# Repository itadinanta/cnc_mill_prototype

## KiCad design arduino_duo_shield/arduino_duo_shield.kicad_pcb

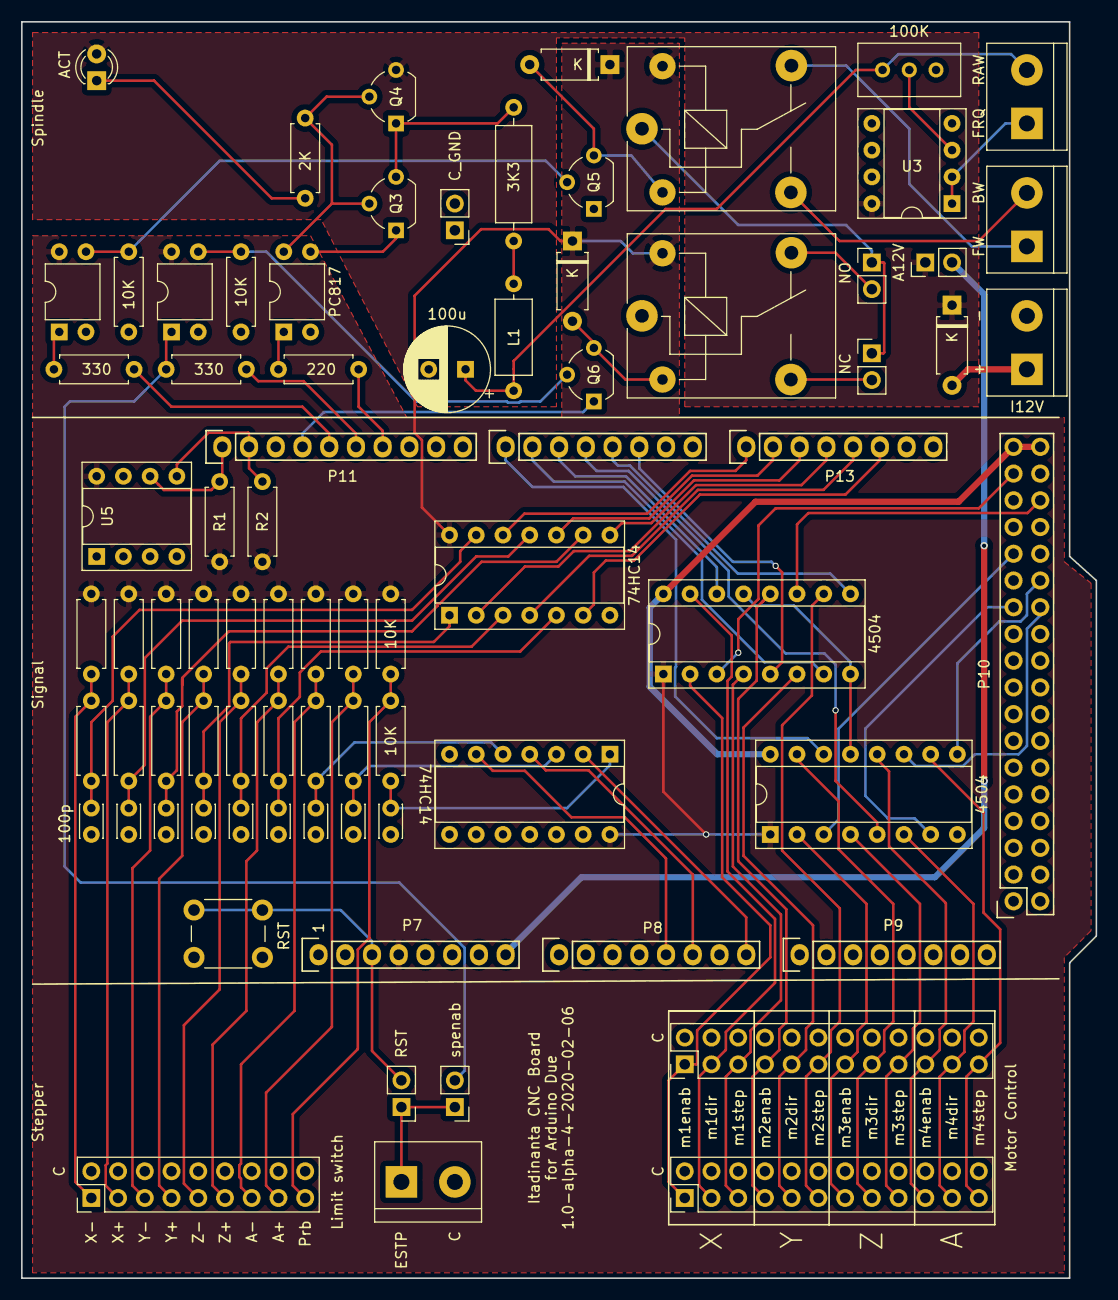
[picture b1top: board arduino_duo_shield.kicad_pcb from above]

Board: 2 copper layers, 102.1 x 119.4 mm, 79 parts (0 on the bottom side), 84 nets.

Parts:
C2, C3, C4, C5, C6, C7, C9, C10, C11: 100p; C_Disc_D3.0mm_W2.0mm_P2.50mm
C8: 100u; CP_Radial_D8.0mm_P3.50mm
D1: LED; LED_D3.0mm
D3, D4, D5: 1N4007; D_A-405_P7.62mm_Horizontal
J2: EStop; TerminalBlock_bornier-2_P5.08mm
J3: Motor_Control; PinHeader_2x12_P2.54mm_Vertical
J4: Limit_Switches; PinHeader_2x09_P2.54mm_Vertical
J5: inverter_freq; TerminalBlock_bornier-2_P5.08mm
J6: inverter_cmd; TerminalBlock_bornier-2_P5.08mm
J8: inverter_power; TerminalBlock_bornier-2_P5.08mm
J9: Motor_Control_Mirror; PinHeader_2x12_P2.54mm_Vertical
JP1, JP2, JP3, JP4: Jumper_NC_Small; PinHeader_1x02_P2.54mm_Vertical
JP5: EStop_RST; PinHeader_1x02_P2.54mm_Vertical
JP6: EStop_spenab; PinHeader_1x02_P2.54mm_Vertical
K2, K3: JQC-3F; Relay_SPDT_SANYOU_SRD_Series_Form_C
L1: 1m; L_Axial_L7.0mm_D3.3mm_P10.16mm_Horizontal_Fastron_MICC
P7: Power; Socket_Strip_Arduino_1x08
P8, P9: Analog; Socket_Strip_Arduino_1x08
P10: Digital; Socket_Strip_Arduino_2x18
P11: PWM; Socket_Strip_Arduino_1x10
P12: PWM; Socket_Strip_Arduino_1x08
P13: Communication; Socket_Strip_Arduino_1x08
Q3, Q5, Q6: 2N7000; TO-92_Wide
Q4: BS250; TO-92_Wide
R1, R2: 1K5; R_Axial_DIN0207_L6.3mm_D2.5mm_P7.62mm_Horizontal
R3, R4, R5, R6, R7, R8, R9, R10, R11, R12, R13, R14, R19, R20, R25, R26, R27, R28, R29, R30: 10K; R_Axial_DIN0207_L6.3mm_D2.5mm_P7.62mm_Horizontal
R15: 220; R_Axial_DIN0207_L6.3mm_D2.5mm_P7.62mm_Horizontal
R21: 2K; R_Axial_DIN0207_L6.3mm_D2.5mm_P7.62mm_Horizontal
R22, R24: 330; R_Axial_DIN0207_L6.3mm_D2.5mm_P7.62mm_Horizontal
R23: 3K3; R_Axial_DIN0309_L9.0mm_D3.2mm_P12.70mm_Horizontal
RV1: 100K; Potentiometer_Bourns_3296W_Vertical
SW1: SW_Push; SW_PUSH_6mm
U1, U2: 4504; DIP-16_W7.62mm_Socket
U3: LM358; DIP-8_W7.62mm_Socket
U4, U6: 74HC14; DIP-14_W7.62mm_Socket
U5: 24LC16; DIP-8_W7.62mm_Socket
U7, U8, U9: PC817; DIP-4_W7.62mm

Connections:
+3V3: D3.1, D4.1, K2.5, K3.5, P7.4, R1.2, R2.1, R3.2, R5.2, R7.2, R9.2, R11.2, R13.2, R19.2, R27.2, R29.2, U1.1, U2.1, U4.14, U5.8, U6.14, U8.4, U9.4
+5V: P10.35, P10.36, U1.16, U2.16
/Debounce_x6/SWAmax+: J4.15, R27.1, R28.2
/Debounce_x6/SWAmin+: J4.13, R29.1, R30.2
/Debounce_x6/SWProbe+: J4.17, R19.1, R20.2
/Debounce_x6/SWXmax+: J4.3, R11.1, R12.2
/Debounce_x6/SWXmin+: J4.1, R13.1, R14.2
/Debounce_x6/SWYmax+: J4.7, R7.1, R8.2
/Debounce_x6/SWYmin+: J4.5, R9.1, R10.2
/Debounce_x6/SWZmax+: J4.11, R3.1, R4.2
/Debounce_x6/SWZmin+: J4.9, R5.1, R6.2
/Level_Shifter/hi_1_1: J3.1, J9.1, U1.2
/Level_Shifter/hi_1_2: J3.3, J9.3, U1.15
/Level_Shifter/hi_1_3: J3.5, J9.5, U1.4
/Level_Shifter/hi_1_4: J3.7, J9.7, U1.12
/Level_Shifter/hi_1_5: J3.9, J9.9, U1.6
/Level_Shifter/hi_1_6: J3.11, J9.11, U1.10
/Level_Shifter/hi_2_1: J3.13, J9.13, U2.2
/Level_Shifter/hi_2_2: J3.15, J9.15, U2.15
/Level_Shifter/hi_2_3: J3.17, J9.17, U2.4
/Level_Shifter/hi_2_4: J3.19, J9.19, U2.12
/Level_Shifter/hi_2_5: J3.21, J9.21, U2.6
/Level_Shifter/hi_2_6: J3.23, J9.23, U2.10
/Reset: JP5.2, P7.3, SW1.2
/SCL: P11.1, R1.1, U5.6
/SDA: P11.2, R2.2, U5.5
/Spindle_VFD_Control/I_PWRSAFE: D1.2, D5.1, JP4.1, Q4.3, U3.8
/Spindle_VFD_Control/ext_estop: JP6.2, R24.2, U9.1
/Spindle_VFD_Control/inverter_12V: D5.2, J8.1
/Spindle_VFD_Control/inverter_bw_switch: J6.2, K3.3
/Spindle_VFD_Control/inverter_frequency_10V: J5.1, U3.1, U3.2
/Spindle_VFD_Control/inverter_frequency_raw_10V: C8.1, J5.2, L1.2, RV1.1
/Spindle_VFD_Control/inverter_fw_switch: J6.1, K3.4
/Spindle_VFD_Control/inverter_gnd: C8.2, J8.2, JP1.1, K2.1, Q3.1, RV1.3, U3.4, U7.3
Amn: P8.5, U6.6
Amx: P8.6, U6.4
GND: C2.1, C3.1, C4.1, C5.1, C6.1, C7.1, C9.1, C10.1, C11.1, J2.2, J3.2, J3.4, J3.6, J3.8, J3.10, J3.12, J3.14, J3.16, J3.18, J3.20, J3.22, J3.24, J4.2, J4.4, J4.6, J4.8, J4.10, J4.12, J4.14, J4.16, J4.18, J9.2, J9.4, J9.6, J9.8, J9.10, J9.12, J9.14, J9.16, J9.18, J9.20, J9.22, J9.24, JP1.2, P7.6, P7.7, P10.1, P10.2, P11.4, Q5.1, Q6.1, R25.2, R26.2, SW1.1, U1.8, U1.13, U2.8, U2.13, U4.7, U5.4, U5.7, U6.7, U7.2, U8.2, U9.2
unnamed: C2.2, R4.1, U4.5
unnamed: C3.2, R6.1, U4.3
unnamed: C4.2, R8.1, U4.1
unnamed: C5.2, R10.1, U4.9
unnamed: C6.2, R12.1, U4.11
unnamed: C7.2, R14.1, U4.13
unnamed: C9.2, R20.1, U6.1
unnamed: C10.2, R28.1, U6.3
unnamed: C11.2, R30.1, U6.5
unnamed: D1.1, R21.1
unnamed: D3.2, K3.2, Q5.3
unnamed: D4.2, K2.2, Q6.3
unnamed: J2.1, JP5.1, JP6.1
unnamed: JP2.1, JP3.1, K3.1
unnamed: JP2.2, K2.3
unnamed: JP3.2, K2.4
unnamed: L1.1, R23.2
unnamed: Q3.2, Q4.2, R21.2, U7.4
unnamed: Q3.3, Q4.1, R23.1
unnamed: Q5.2, R25.1, U8.3
unnamed: Q6.2, R26.1, U9.3
unnamed: R15.2, U7.1
unnamed: R22.2, U8.1
unnamed: RV1.2, U3.3
Probe: P8.8, U6.2
Xmn: P13.1, U4.12
Xmx: P13.2, U4.10
Ymn: P13.3, U4.8
Ymx: P13.4, U4.2
Zmn: P13.5, U4.4
Zmx: P13.6, U4.6
ext_12v: JP4.2, P7.8
m1dir: P12.3, U1.14
m1enab: P10.33, U1.3
m1step: P12.6, U1.5
m2dir: P12.2, U1.7
m2enab: P10.32, U1.11
m2step: P12.5, U1.9
m3dir: P12.1, U2.14
m3enab: P10.27, U2.3
m3step: P12.4, U2.5
m4dir: P10.23, U2.7
m4enab: P10.24, U2.11
m4step: P10.26, U2.9
spdir: P11.5, R22.1
spenab: P11.6, R24.1
sppwm: P11.7, R15.1

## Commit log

2019-07-20 Added holes as pockets
2019-07-21 Basic C-Beam profile
2019-07-21 Adds corner side by side
2019-07-23 Last V-slot sketch
2019-08-21 Add debounce x6 for limit switches
2019-08-31 Add labels and footprints
2019-09-01 Replace 4x 6x connectors with 1x 24x, add firmware
2019-09-02 Add firmware to fix the power-on bug
2019-09-06 Fixed power pins
2019-09-11 Use only 1 VPOW in spindle control
2019-09-12 Power block to PCB
2019-09-14 Add PCB front/back for spindle controls
2019-09-21 Complete wiring
2019-09-22 Plot layouts to upload to to JLBPCB
2019-10-07 Add ketch for box container
2019-10-12 Fix diode symbol in schematic
2019-11-03 Add physical workbench diagrams
2019-11-03 Shoulder
2019-11-04 Complete workbench frame sketches
2019-11-04 CAD plans
2019-11-09 Test cuts (mostly flattening)
2019-11-20 Prototype filter-based PWM->voltage DAC
2019-11-25 Add sketch for the spindle bracket adapter
2019-12-04 Recalculate paths of spindle adapter
2019-12-23 Ready to build the WorkBee
2019-12-23 Add signal mirror and control jumpers
2019-12-27 Add design and paths for simple inverter holding panel
2019-12-29 Route all paths
2019-12-29 Add silk screen labels and version number
2019-12-30 Generate gerber files for 1.0-alpha-1
2019-12-30 Send to JLCPCB
2020-01-08 Add flatten operation
2020-01-08 Add voltage follower as end stage of spindle control
2020-01-12 Expose raw analog frequency control
2020-01-14 Add support for spindle estop
2020-01-14 Adjust labels
2020-02-03 Add support for 24LC16 EEPROM
2020-02-06 Tidy up, generate plots for JLCPCB, alpha 4
2020-02-16 Edit touch plate, redo holes in bed
2020-02-17 Generate helix cuts (Example)
2020-02-19 Split edge from body holes and bores
2020-02-22 Add flattening
2020-02-23 Generate gcode for holes and bed flatten
2020-03-01 Regenerate gcode for flatten with variant
2020-03-03 Draw support board for ATX case
2020-03-04 Add Arduino Due footprint
2020-03-04 Add shield constraint
2020-03-07 Add layout for larger booster
2020-03-09 Add ammeter holder panel
2020-03-09 Tweak view
2020-03-10 Create counterbore om the back plane
2020-03-13 Cut ATX board upgrade
